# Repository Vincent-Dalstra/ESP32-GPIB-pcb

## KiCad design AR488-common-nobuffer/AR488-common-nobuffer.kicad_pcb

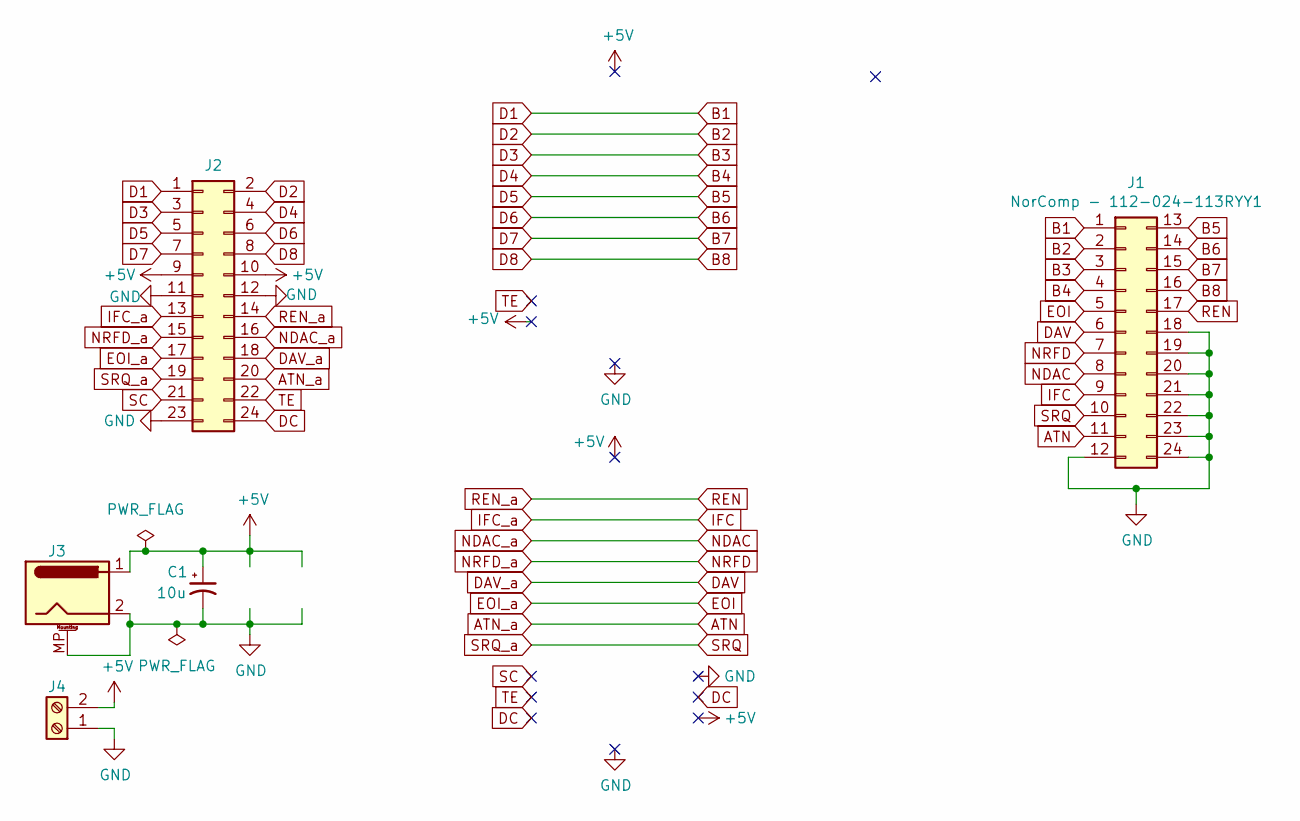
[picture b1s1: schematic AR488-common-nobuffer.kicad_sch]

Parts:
C1: 10u; CP_EIA-7132-20_AVX-U
J1: NorComp - 112-024-113RYY1; CENTRONICS-24
J2: Conn_02x12_Odd_Even; PinSocket_2x12_P2.54mm_Vertical
J3: Barrel_Jack; BarrelJack_CUI_PJ-063AH_Horizontal
J4: Screw_Terminal_01x02; TerminalBlock_Altech_AK300-2_P5.00mm

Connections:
+5V: C1.1, J2.9, J2.10, J3.1, J4.2
ATN: J1.11, J2.20
B1: J1.1, J2.1
B2: J1.2, J2.2
B3: J1.3, J2.3
B4: J1.4, J2.4
B5: J1.13, J2.5
B6: J1.14, J2.6
B7: J1.15, J2.7
B8: J1.16, J2.8
DAV: J1.6, J2.18
DC: J2.24
EOI: J1.5, J2.17
GND: C1.2, J1.12, J1.18, J1.19, J1.20, J1.21, J1.22, J1.23, J1.24, J2.11, J2.12, J2.23, J3.2, J3.MP (MountPin), J4.1
IFC: J1.9, J2.13
NDAC: J1.8, J2.16
NRFD: J1.7, J2.15
REN: J1.17, J2.14
SC: J2.21
SRQ: J1.10, J2.19
TE: J2.22

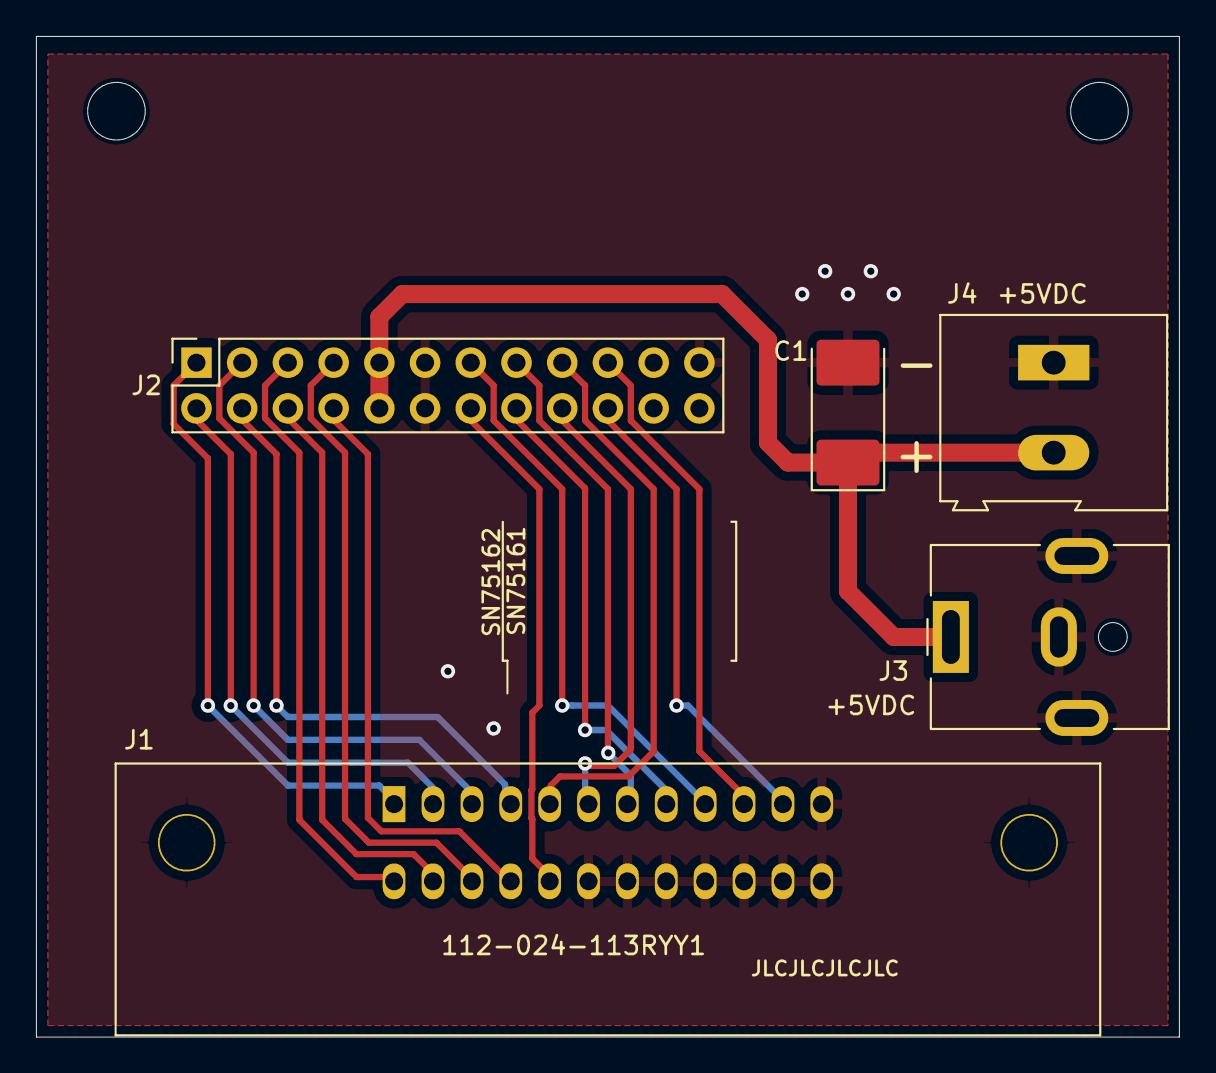
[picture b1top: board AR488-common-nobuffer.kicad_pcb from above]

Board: 2 copper layers, 63.5 x 55.6 mm, 5 parts (0 on the bottom side), 18 nets.

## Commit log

2023-07-10 Added bufferless-version of carrier board
    Intention is to experiment wiht a single device, and see if it works
    well.
2023-07-10 Added topboard for ESP32-S3 devkits
    Designed for the devkitC, but should also work with the devkitM;
    specifically picked pins that work with both of them. GPIO's are
    different, though.
2023-07-10 Sent to board fab
    No version markings. 5x of each:
    - Common
    - Common-nobuffer
    - ESP32-devkitc
    - ESP32-S3-devkitc

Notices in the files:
AR488-common-nobuffer/AR488-common-nobuffer.kicad_pcb:
CC BY-SA 3.0
